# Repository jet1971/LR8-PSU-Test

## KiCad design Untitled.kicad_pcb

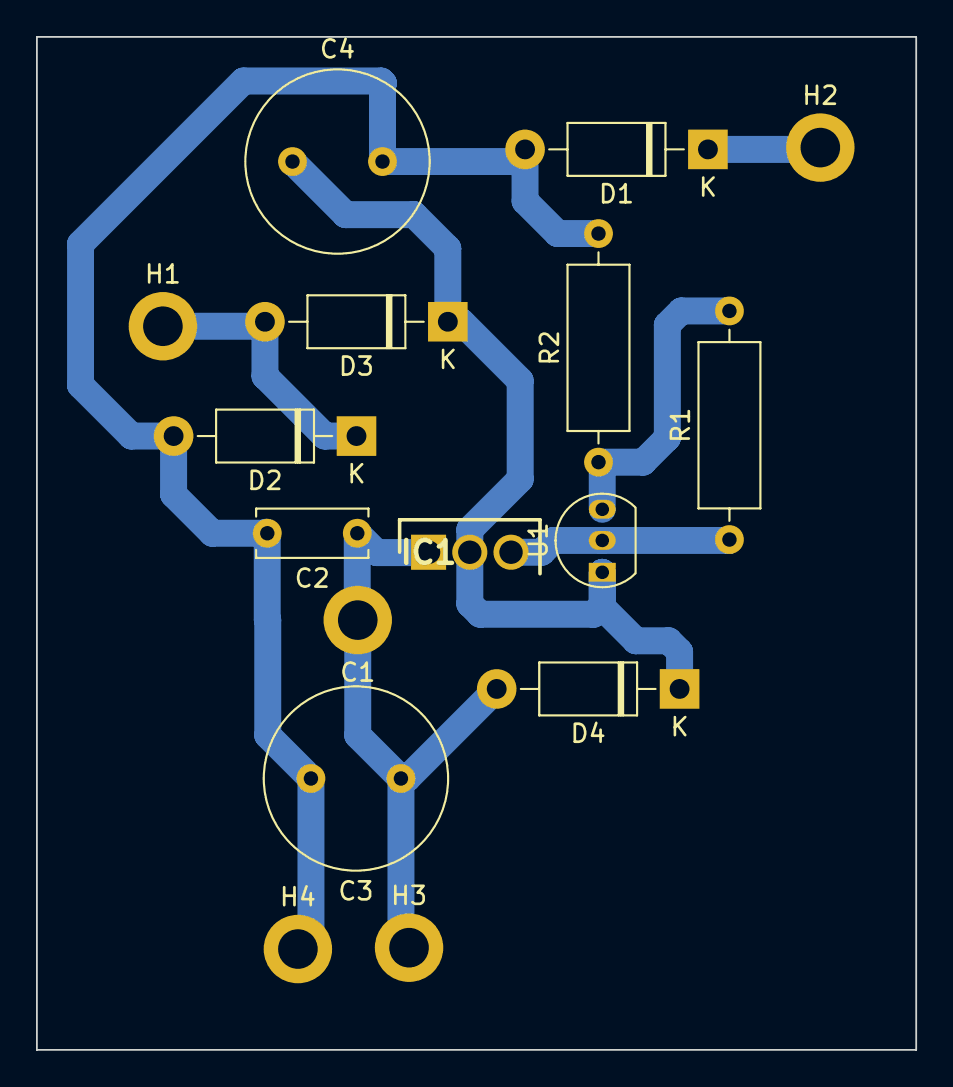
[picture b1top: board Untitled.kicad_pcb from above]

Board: 2 copper layers, 48.8 x 56.3 mm, 16 parts (0 on the bottom side), 7 nets.

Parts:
C1: 100n; MountingHole_2.2mm_M2_DIN965_Pad
C2: 100n; C_Disc_D6.0mm_W2.5mm_P5.00mm
C3: 470uF 16v; C_Radial_D10.0mm_H16.0mm_P5.00mm
C4: 2.2uF 450v; C_Radial_D10.0mm_H12.5mm_P5.00mm
D1, D2, D3: D; D_DO-41_SOD81_P10.16mm_Horizontal
D4: IN4004; D_DO-41_SOD81_P10.16mm_Horizontal
H1: Source +; MountingHole_2.2mm_M2_DIN965_Pad
H2: Source -; MountingHole_2.2mm_M2_DIN965_Pad
H3: + 5 Volts; MountingHole_2.2mm_M2_DIN965_Pad
H4: GND; MountingHole_2.2mm_M2_DIN965_Pad
IC1: MJE340G; TO229P300X760X1364-3P
R1: 4k3 1 %; R_Axial_DIN0309_L9.0mm_D3.2mm_P12.70mm_Horizontal
R2: 15k 1 %; R_Axial_DIN0309_L9.0mm_D3.2mm_P12.70mm_Horizontal
U1: LR8N3-G; TO-92_Inline

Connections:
GND: C2.2, C3.2, C4.2, D1.2 (A), D2.2 (A), H4.1, R2.2
unnamed: C1.1, C2.1, C3.1, D4.2 (A), H3.1, IC1.1 (EMITTER)
unnamed: C4.1, D3.1 (K), D4.1 (K), IC1.2 (COLLECTOR), U1.1 (IN)
unnamed: D1.1 (K), H2.1
unnamed: D2.1 (K), D3.2 (A), H1.1
unnamed: IC1.3 (BASE), R1.1, U1.2 (OUT)
unnamed: R1.2, R2.1, U1.3 (ADJ)

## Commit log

2022-09-03 LR8 PSU test
